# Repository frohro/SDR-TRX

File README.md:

# SDR-TRX Digital Modes Transceiver, 2023-2024
## Philosophy and Design Goals
This SDR is a prototype hardware platform to assist in developing a low-cost transceiver for digital modes (FT8, JSTcall, WSPR, CW, etc) that do not require linear amplification like SSB.  This is designed for amateur radio enthusiasts who view their hobby as an avenue for experimenting, who like building things, and have an interest in HF radio propagation.  The idea is to use a laptop and mainstream (actively maintained) existing software as the display and for the DSP needed.  The hardware described here will fill out the rest of the transceiver.  The assumption is that most hams will have a PC of some kind already, and this is an easy and cheap way to get on the air using the digital modes and their PC.
I am also using this as a platform to demonstrate to my students how to do an electronic design project.  It is hoped a transceiver based on this prototype platform will be inexpensive enough that third-world hams or those with few funds to spend on their hobby would find it attractive.  JLCPCB built five of these for me for a little over $100.  This project is built using designs previously published and would not be possible without them.  The next section is meant to be a short review of some of the projects I found especially useful.
### Previous Work
#### Especially Relevant Work
* [WSJT-Transceiver](https://github.com/agustinmartino/wsjt_transceiver/blob/master/README.md)
* [Quisk SDR Software](https://james.ahlstrom.name/quisk/)
* [WSJT-X Low S/N Digital Mode Decoding Software](https://wsjt.sourceforge.io/)
* [Fldigi](http://www.w1hkj.com/FldigiHelp/index.html)
* [DL2MAN Sandwich](https://dl2man.de/sample-page/)
* [PE1NNZ uSDX](https://github.com/threeme3/usdx)
* [A Comparison of Affordable Self-Assembled SDR Receivers](https://fweb.wallawalla.edu/~frohro/ClassHandouts/Electronics/A%20Comparison%20of%20Affordable,%20Self-Assembled%20%20Software-Defined%20Radio%20Receivers%20Using%20Quadrature%20Sampling%20Down-Conversion.pdf)
* [QRP Labs QDX Transceiver](https://www.qrp-labs.com/qdx.html) (This transceiver is quite similar.)
#### More General but Useful Work
*  [Easy-Transceiver](https://github.com/kholia/Easy-Transceiver])
* [Etherkit JTEncode](https://github.com/etherkit/JTEncode)
* [Etherkit Si5351](https://github.com/etherkit/Si5351Arduino)

###
The basic block diagram showing how this SDR interfaces with a PC is shown below.  (Sorry the photos do not show up on GitHub's README here.  To see them, download the progress notes here: https://github.com/frohro/SDR-TRX/blob/main/SDR-TRX-Readme-Progress-Notes.html and then open them in your browser, or get the iPython Progress Notes for a more up to date version and use JupyterLab or similar tool to read them.)

A clone of the Silicon Labs, Si5351a, the MS5351M is used as the local oscillator for the QSD down converter.  The resultant audio frequency data is sent to the PC where Quisk demodulates it and sends it on to WSJT-X or Fldigi for decoding.  The MS5351M's third oscillator is used to generate the digital signals on transmit.  These signals are amplified by a class E circuit for the 20-meter band.  Throughout the unit, there are features that provide stepping stones toward the final goal.  For example, an output is provided to allow the sound data to be sent to the PC where a sound card on the PC converts the sound signal to digital samples.  A Raspberry Pi Pico or Pico W is used on the SDR to control the MS5351M local oscillator and exciter, sample the receiver audio data using a PCM1808 ADC, and send the sampled data to the PC for processing.  It also receives transmit data from the PC to allow transmission of the digital signals desired.

The Kicad project SDR-TRX contains the hardware documentation, including the schematic diagram and the printed circuit board.  The software is still in development.

##  Transmitter 
The MS5351M, a Si5351a clone, generates a digitally transmitted signal (and the harmonics you expect) on its third output.  It is used to drive a set of CMOS inverters that in turn drive a MOSFET class E amplifier for 20 meters. 

### Class E Amplifier
The design started with the DL2MAN sandwich Class E amplifier for 20 meters.  LTspice was employed to try and minimize the number of values of Extended Parts capacitors needed from JLCPCB while still maintaining a decent efficiency, power output, and harmonic attenuation.  The value of the capacitor that seemed to be best was a 120 pF 100V 1% COG multilayer monolithic capacitor.  We paralleled a bunch to make the amplifier we ended up with.  It was chosen first for harmonic suppression, second for power output, and lastly for efficiency, with the constraint of using only one value of capacitor.  The simulation has about 50 dB of harmonic attenuation, about a watt of output, and an efficiency of 75%.  See the simulation below which is called Class E.asc in the Simulation folder.

This simulation shows the efficiency and output power.

This is the FFT of the antenna voltage.

There is an I2C voltage and current monitor, the INA219A, that should allow measuring the DC power used by the class E amplifier so LTspice simulations can be verified for accuracy easily.

## Receiver
The receiver used was the [QSD Tayloe-type](https://www.norcalqrp.org/files/Tayloe_mixer_x3a.pdf) design using both inverting and inverting inputs.  The inverting input has a lower input impedance and so is more of a current amplifier.  The non-inverting amplifier has a high input impedance, and so acts as a voltage amplifier.  The low-frequency gain of the inverting amplifier is $\frac{-R_f}{R_i}$ and the non-inverting amplifier has a gain of $1 + \frac{R_f}{R_i}$ so the CMRR is  not as good as a fully differential amplifier, but we are just trying to amplify the signal not null out any common mode signal.  We need to keep the DC to $\frac {4.5V}{2}$ and the $1$ term perfectly does this for us for the common mode DC voltage.  There is a gain for the mixer of $1/4$ because the state space average of the switched voltage at the output of the mixer is a quarter of the input voltage.  The gain is initially set to about 20 between the antenna and I or Q.  These signals go into the soundcard or the onboard ADC, a PCM1808.

The MS5351M generates in-phase and quadrature signals for the SN74CBT3253 four-to-one analog switch mixer.

The sampling capacitors provide a low pass filter for the signal, and the cutoff frequency is $1/(2\pi R_f 4 C)$.  The factor of four comes about because the sampling capacitors only get charged a quarter of the time, or equivalently, there are four of them to charge.  The resistance, $R_i$, is the antenna impedance plus the 10 ohms on the inverting input.  The feedback capacitors, $C_f$ add another pole of low pass filter to the signal.  The cutoff frequency of these filters is $1/(2\pi R_f C_f)$.

There are two antenna inputs (BNC connectors), one on a transmit/receive switch that uses the Class E filter to try and filter the received signal, and another one that bypasses the filter that can be used when we want to listen to more than just 20 meters.  It can also suffice to do real-world testing to see which is preferable.

An LDO linear regulator powered by the USB 5 volts or the external 12-volt power supply provides a 4.5 volt low noise power for the analog parts in the receiver.  When the 12-volt input is used the USB power supply is disconnected by some Schottky diodes and two possible regulators drop the voltage to about 5.8 volts to run the rest of the radio except the class E PA stage.  These are selected by an I/O line from the processor or by not populating the undesired supply.  The two options are an SMPS buck regulator or a 7805 linear regulator that is not as efficient but should not produce switching noise. We will experiment to see which we like and choose that one.

There are several ground loop suppression strategies available.  The filtered antenna uses a transformer.  In other places, a jumper is provided to allow a single ground connection through the power supply.  

## Control Circuitry
The control of the SDR comes from the operator via the PC interface software (Quisk, for example), which sends the data to the SDR via USB UART or via WIFI.  The MCU that we chose is the Raspberry Pi Pico or Pico W if WIFI is desired.  It controls the MS5351M programmable oscillator using I2C and uses the INA219 to measure the current and voltage of the power amplifier.  It also reads the ADC via I2S and transfers that data to the PC where Quisk or a similar program demodulates it.  For the Pico, we are using C++ and the Earl E. Philhower, [Arduido-Pico](https://arduino-pico.readthedocs.io/en/latest/index.html) development library.  The easiest way to get started is to use the Arduino IDE, but VScode with Github Copilot there are a lot more features.  You have to [read how to make the Arduino-Pico](https://arduino-pico.readthedocs.io/en/latest/platformio.html) code work with VScode.  The software needs a lot more attention, but that is the point of a software-defined radio.

### PCB
The PCB has test points and uses components I found still available on JLCPCB.  That accounts for why a mix or 0603 and 0805 components, and why there are a lot of 120pF and 4.7nF caps in parallel.

The cutout is for the WIFI antenna if a Pico W is used.

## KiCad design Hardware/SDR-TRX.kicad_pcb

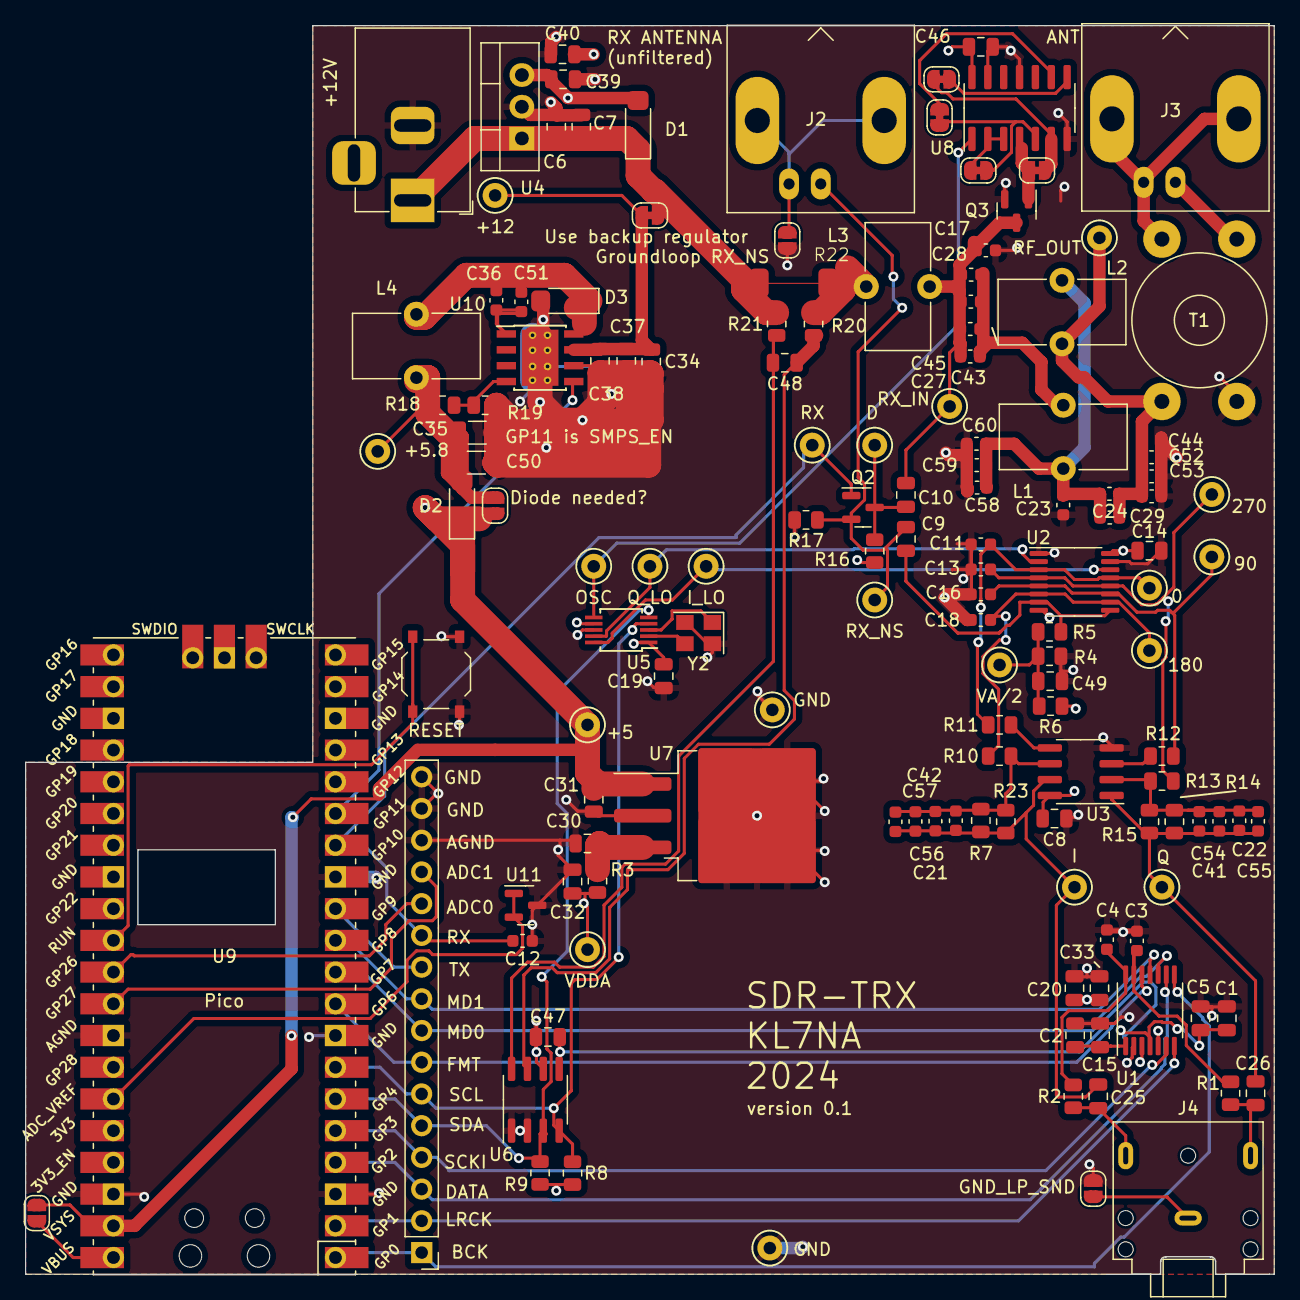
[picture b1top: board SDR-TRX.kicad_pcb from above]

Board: 4 copper layers, 100.0 x 100.0 mm, 141 parts (0 on the bottom side), 69 nets.

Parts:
C1, C2, C6, C20, C30, C32, C39: 10uF; C_0805_2012Metric
C3, C4, C11, C12, C13, C16, C18, C36, C51: 4.7nF; C_0603_1608Metric
C5, C7, C8, C9, C10, C14, C15, C19, C31, C33, C40, C46, C47, C48, C49: 0.1u; C_0805_2012Metric
C17, C21, C22, C23, C24, C27, C28, C29, C41, C42, C43, C44, C45, C52, C53, C54, C55, C56, C57, C58, C59, C60: 120p; C_0603_1608Metric
C25, C26: 1uF; C_0805_2012Metric
C34, C37, C38: 22uF; C_0805_2012Metric
C35, C50: 100uF; C_1206_3216Metric
D1, D2, D3: SS54; DO-214AC-Rob
J1: Debug Connector; PinHeader_1x16_P2.54mm_Vertical
J2, J3: BNC; BNC_Amphenol_B6252HB-NPP3G-50_Horizontal
J4: Audio Out to Soundcard; Jack_3.5mm_CUI_SJ1-3523N_Horizontal
J6: +12V; BarrelJack_Horizontal
JP1: GND_LP_SND; SolderJumper-2_P1.3mm_Open_RoundedPad1.0x1.5mm
JP2: Groundloop RX_NS; SolderJumper-2_P1.3mm_Open_RoundedPad1.0x1.5mm
JP4: Use backup regulator; SolderJumper-2_P1.3mm_Bridged_RoundedPad1.0x1.5mm
JP5: CM1A; SolderJumper-2_P1.3mm_Bridged_RoundedPad1.0x1.5mm
JP6: CM1B; SolderJumper-2_P1.3mm_Bridged_RoundedPad1.0x1.5mm
JP7: CM2B; SolderJumper-2_P1.3mm_Bridged_RoundedPad1.0x1.5mm
JP8: CM2A; SolderJumper-2_P1.3mm_Bridged_RoundedPad1.0x1.5mm
JP9: Diode needed?; SolderJumper-2_P1.3mm_Open_RoundedPad1.0x1.5mm
JP12: USB Only; SolderJumper-2_P1.3mm_Open_RoundedPad1.0x1.5mm
L1: .48uH 12t/T-37-6; L_Toroid_Vertical_L10.0mm_W5.0mm_P5.08mm
L2: .19uH 5t/T37-6; L_Toroid_Vertical_L10.0mm_W5.0mm_P5.08mm
L3: 200u 22t FT-37-43; L_Toroid_Vertical_L10.0mm_W5.0mm_P5.08mm
L4: 15uH 7t/FT37-43; L_Toroid_Vertical_L10.0mm_W5.0mm_P5.08mm
Q2, Q3: IRLML2060; SOT-23
R1, R2: 200; R_0805_2012Metric
R3: 1; R_0805_2012Metric
R4, R5, R6, R18: 10k; R_0805_2012Metric
R7, R14, R15, R23: 3.9k; R_0805_2012Metric
R8, R9: 4.7k; R_0805_2012Metric
R10, R11, R12, R13, R20, R21: 10; R_0805_2012Metric
R16: 470k; R_0805_2012Metric
R17: 1k; R_0805_2012Metric
R19: 2.67k; R_0805_2012Metric
R22: 0.03 shunt; .03 Shunt
SW2: RESET; SW_Push_1P1T_XKB_TS-1187A
T1: 1:1 FT37-43; Transformer_Toroid_Horizontal_D10.5mm_Amidon-T37
TP1: I_LO; TestPoint_Keystone_5000-5004_Miniature
TP2: Q_LO; TestPoint_Keystone_5000-5004_Miniature
TP4: RX_NS; TestPoint_Keystone_5000-5004_Miniature
TP5: 180; TestPoint_Keystone_5000-5004_Miniature
TP6: 0; TestPoint_Keystone_5000-5004_Miniature
TP7: 270; TestPoint_Keystone_5000-5004_Miniature
TP8: 90; TestPoint_Keystone_5000-5004_Miniature
TP9, TP13: GND; TestPoint_Keystone_5000-5004_Miniature
TP10: I; TestPoint_Keystone_5000-5004_Miniature
TP11: Q; TestPoint_Keystone_5000-5004_Miniature
TP12: VA/2; TestPoint_Keystone_5000-5004_Miniature
TP14: RX_IN; TestPoint_Keystone_5000-5004_Miniature
TP15: D; TestPoint_Keystone_5000-5004_Miniature
TP16: OSC; TestPoint_Keystone_5000-5004_Miniature
TP17: RX; TestPoint_Keystone_5000-5004_Miniature
TP18: RF_OUT; TestPoint_Keystone_5000-5004_Miniature
TP27: VDDA; TestPoint_Keystone_5000-5004_Miniature
TP28: +5; TestPoint_Keystone_5000-5004_Miniature
TP34: +5.8; TestPoint_Keystone_5000-5004_Miniature
TP35: +12; TestPoint_Keystone_5000-5004_Miniature
U1: PCM1808PWR; TSSOP-14_4.4x5mm_P0.65mm
U2: SN74CBT3253CPWR; TSSOP-16_4.4x5mm_P0.65mm
U3: OPA1612AxD; SOIC-8_3.9x4.9mm_P1.27mm
U4: LM7805_TO220; TO-220-3_Vertical
U5: MS5351M; MSOP-10_3x3mm_P0.5mm
U6: INA219AxD; SOIC-8_3.9x4.9mm_P1.27mm
U7: LM2937xS; TO-263-3_TabPin2
U8: 74HC14; SOIC-14_3.9x8.7mm_P1.27mm
U9: Pico; RPi_Pico_SMD_TH
U10: TPS5430DDA; TI_SO-PowerPAD-8_ThermalVias
U11: CJ432; SOT-23
Y2: X322525MSB4SI; Crystal_SMD_3225-4Pin_3.2x2.5mm

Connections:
+3.3V: C1.1, C5.2, C19.2, C47.2, R8.2, R9.2, U1.4 (VDD), U5.1 (VDD), U5.7 (VDDO), U6.5 (VS), U9.36 (3V3)
+5V: C31.1, C39.1, C40.2, C46.2, D1.2 (A), D2.1 (K), JP9.2 (B), JP12.2 (B), TP28.1, U4.3 (VO), U7.1 (VI), U8.14 (VCC), U9.39 (VSYS)
+12V: C34.1, C37.1, C38.1, JP4.2 (B), TP35.1, U10.7 (VIN)
/ADC0: J1.12, U9.31 (GPIO26_ADC0)
/ADC1: J1.13, U9.32 (GPIO27_ADC1)
/BCK: J1.1, U1.8 (BCK), U9.1 (GPIO0)
/Class E PA/OSC: TP16.1, U5.6 (CLK2), U8.1
/Class E PA/RX_IN: C10.1, C17.2, C27.2, C28.2, C43.2, C45.2, L3.2, Q3.3 (D), TP14.1
/DATA: J1.3, U1.9 (DOUT), U9.4 (GPIO2)
/FMT: J1.7, U1.12 (FMT), U9.9 (GPIO6)
/LRCK: J1.2, U1.7 (LRCK), U9.2 (GPIO1)
/MD0: J1.8, U1.10 (MD0), U9.10 (GPIO7)
/MD1: J1.9, U1.11 (MD1), U9.11 (GPIO8)
/RX: C12.2, J1.11, Q2.1 (G), TP17.1, U9.14 (GPIO10)
/Receiver/I_OUT: C25.1, J4.R, R2.1
/Receiver/Q_OUT: C26.1, J4.T, R1.1
/Receiver/RX_NS: C9.1, J2.1 (In), Q2.2 (S), R17.1, TP4.1
/SCKI: J1.4, U1.6 (SCKI), U9.5 (GPIO3)
/SCL: J1.6, R8.1, U5.4 (SCL), U6.4 (SCL), U9.7 (GPIO5)
/SDA: J1.5, R9.1, U5.5 (SDA), U6.3 (SDA), U9.6 (GPIO4)
/SMPS_EN: U9.15 (GPIO11), U10.5 (EN)
/TX: J1.10, U9.12 (GPIO9)
GND: C1.2, C2.2, C3.1, C4.1, C5.1, C6.2, C7.1, C8.1, C11.1, C12.1, C13.1, C14.1, C15.1, C16.1, C17.1, C18.1, C19.1, C20.2, C23.2, C30.2, C31.2, C32.2, C33.1, C34.2, C35.2, C37.2, C38.2, C39.2, C40.1, C44.2, C46.1, C47.1, C49.1, C50.2, C52.2, C53.2, C58.2, C59.2, C60.2, D3.2 (A), J1.14, J1.15, J1.16, J6.2, JP1.1 (A), JP2.1 (A), Q3.2 (S), R4.2, R17.2, R19.2, SW2.1 (A), T1.2 (AB), TP9.1, TP13.1, U1.2 (AGND), U1.5 (DGND), U2.1 (1~OE), U2.8 (GND), U2.15 (2~OE), U3.4 (V-), U4.2 (GND), U5.8 (GND), U6.1 (A1), U6.2 (A0), U6.6 (GND), U7.2 (GND), U8.7 (GND), U8.11, U8.13, U9.3 (GND), U9.8 (GND), U9.13 (GND), U9.33 (AGND), U9.38 (GND), U10.6 (GND), U10.9 (GNDPAD), U11.3 (A), Y2.2, Y2.4
unnamed: C21.2, C25.2, C42.2, C56.2, C57.2, R7.1, R23.1, TP10.1, U3.7
unnamed: C22.2, C26.2, C41.2, C54.2, C55.2, R14.1, R15.1, TP11.1, U3.1
unnamed: C23.1, C24.2, C29.2, C58.1, C59.1, C60.1, L1.2, L2.1
unnamed: C27.1, C28.1, C43.1, C45.1, L1.1
unnamed: C49.2, R4.1, R5.1, R6.2, TP12.1
unnamed: C6.1, C7.2, D1.1 (K), J6.1, JP4.1 (A), R21.2, R22.2, U4.1 (VI)
unnamed: C35.1, C50.1, D2.2 (A), JP9.1 (A), L4.2, R18.1, TP34.1
unnamed: C36.1, C51.1, D3.1 (K), L4.1, U10.8 (PH)
unnamed: J2.2 (Ext), JP2.2 (B)
unnamed: J3.2 (Ext), T1.3 (SA)
unnamed: J3.1 (In), T1.4 (SB)
unnamed: J4.S, JP1.2 (B)
unnamed: JP5.1 (A), U8.2, U8.3
unnamed: JP5.2 (B), JP8.1 (A), U8.5
unnamed: JP6.1 (A), Q3.1 (G), U8.4
unnamed: JP6.2 (B), JP7.1 (A), U8.6
unnamed: JP7.2 (B), U8.8
unnamed: JP8.2 (B), U8.9
unnamed: JP12.1 (A), U9.40 (VBUS)
unnamed: L3.1, R20.2, R22.1
unnamed: C10.2, Q2.3 (D), R16.2, TP15.1
unnamed: SW2.2 (B), U9.30 (RUN)
unnamed: C24.1, C29.1, C44.1, C52.1, C53.1, L2.2, T1.1 (AA), TP18.1
unnamed: C3.2, R1.2, U1.13 (VINL)
unnamed: C4.2, R2.2, U1.14 (VINR)
unnamed: C2.1, C15.2, U1.1 (VREF)
unnamed: C9.2, R5.2, U2.7 (1A), U2.9 (2A)
unnamed: C18.2, R10.2, TP5.1, U2.6 (1B1), U2.10 (2B1)
unnamed: C16.2, R12.2, TP8.1, U2.5 (1B2), U2.11 (2B2)
unnamed: C13.2, R13.2, TP7.1, U2.4 (1B3), U2.12 (2B3)
unnamed: C11.2, R11.2, TP6.1, U2.3 (1B4), U2.13 (2B4)
unnamed: TP1.1, U2.14 (S0), U5.10 (CLK0)
unnamed: TP2.1, U2.2 (S1), U5.9 (CLK1)
unnamed: R12.1, U3.3 (+)
unnamed: C22.1, C41.1, C54.1, C55.1, R13.1, R14.2, R15.2, U3.2 (-)
unnamed: R11.1, U3.5 (+)
unnamed: C21.1, C42.1, C56.1, C57.1, R7.2, R10.1, R23.2, U3.6 (-)
unnamed: U5.2 (XA), Y2.3
unnamed: U5.3 (XB), Y2.1
unnamed: C48.2, R21.1, U6.8 (IN+)
unnamed: C48.1, R20.1, U6.7 (IN-)
unnamed: C30.1, R3.2, U7.3 (VO)
unnamed: C36.2, C51.2, U10.1 (BOOT)
unnamed: R18.2, R19.1, U10.4 (VSENSE)
unnamed: U9.35 (ADC_VREF), U11.1 (REF), U11.2 (K)
VDDA: C8.2, C14.2, C20.1, C32.1, C33.2, R3.1, R6.1, R16.1, TP27.1, U1.3 (VCC), U2.16 (VCC), U3.8 (V+)

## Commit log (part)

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2024-04-23 Apr 22, 2024, 9:16 PM
2024-04-23 Apr 22, 2024, 9:19 PM
2024-04-23 Apr 22, 2024, 9:21 PM
2024-04-23 Apr 22, 2024, 9:23 PM
2024-04-23 Apr 22, 2024, 9:24 PM
2024-04-23 Apr 22, 2024, 9:25 PM
2024-04-23 Apr 22, 2024, 9:36 PM
2024-04-23 Apr 22, 2024, 9:41 PM
2024-04-23 Apr 22, 2024, 9:42 PM
2024-04-23 Apr 22, 2024, 9:44 PM
2024-04-23 Apr 22, 2024, 9:50 PM
2024-04-23 Apr 22, 2024, 9:55 PM
2024-04-23 Apr 22, 2024, 10:01 PM
2024-04-23 Apr 22, 2024, 10:03 PM
2024-04-23 Apr 22, 2024, 10:12 PM
2024-04-23 Apr 22, 2024, 10:14 PM
2024-04-23 Apr 22, 2024, 10:25 PM
2024-04-23 Apr 23, 2024, 8:54 AM
2024-04-23 Apr 23, 2024, 10:43 AM
2024-04-23 Apr 23, 2024, 10:46 AM
2024-04-23 Apr 23, 2024, 11:05 AM
2024-04-23 Apr 23, 2024, 11:08 AM
2024-04-23 Apr 23, 2024, 11:10 AM
2024-04-23 Apr 23, 2024, 11:37 AM
2024-04-25 Apr 24, 2024, 10:28 PM
2024-04-25 Apr 25, 2024, 7:40 AM
2024-04-25 Apr 25, 2024, 8:10 AM
2024-04-25 Apr 25, 2024, 8:48 AM
2024-04-25 Apr 25, 2024, 8:53 AM
2024-04-25 Apr 25, 2024, 8:56 AM
2024-04-25 Apr 25, 2024, 9:09 AM
2024-04-25 Apr 25, 2024, 9:10 AM
2024-04-25 Apr 25, 2024, 9:12 AM
2024-04-25 Apr 25, 2024, 10:24 AM
2024-04-25 Apr 25, 2024, 10:27 AM
2024-04-25 Apr 25, 2024, 10:43 AM
2024-04-25 Apr 25, 2024, 10:50 AM
2024-04-25 Apr 25, 2024, 10:53 AM
2024-04-25 Apr 25, 2024, 10:57 AM
2024-04-25 Apr 25, 2024, 10:59 AM
2024-04-25 Apr 25, 2024, 11:00 AM
2024-04-25 Apr 25, 2024, 11:02 AM
2024-04-25 Apr 25, 2024, 11:04 AM
2024-04-25 Apr 25, 2024, 11:06 AM
2024-04-25 Apr 25, 2024, 11:08 AM
2024-04-25 Apr 25, 2024, 11:09 AM
2024-04-25 Apr 25, 2024, 11:11 AM
2024-04-25 Apr 25, 2024, 11:14 AM
2024-04-25 Apr 25, 2024, 11:21 AM
2024-04-25 Apr 25, 2024, 11:23 AM
2024-04-25 Apr 25, 2024, 11:25 AM
2024-04-25 Apr 25, 2024, 11:26 AM
2024-04-25 Apr 25, 2024, 11:27 AM
2024-04-25 Apr 25, 2024, 11:31 AM
2024-04-25 Apr 25, 2024, 11:34 AM
2024-04-25 Apr 25, 2024, 11:36 AM
2024-04-25 Apr 25, 2024, 11:39 AM
2024-04-25 Apr 25, 2024, 11:40 AM
2024-04-25 Apr 25, 2024, 11:41 AM
2024-04-25 Apr 25, 2024, 11:43 AM
2024-04-25 Apr 25, 2024, 11:45 AM
2024-04-25 Apr 25, 2024, 11:46 AM
2024-04-25 Apr 25, 2024, 12:27 PM
2024-04-25 Apr 25, 2024, 12:31 PM
2024-04-25 Apr 25, 2024, 12:35 PM
2024-04-25 Apr 25, 2024, 12:36 PM
2024-04-25 Apr 25, 2024, 12:42 PM
2024-04-25 Apr 25, 2024, 12:43 PM
2024-04-25 Apr 25, 2024, 1:20 PM
2024-04-25 Apr 25, 2024, 1:22 PM
2024-04-25 Apr 25, 2024, 1:31 PM
2024-04-25 Apr 25, 2024, 1:38 PM
2024-04-25 Apr 25, 2024, 1:39 PM
2024-04-25 Apr 25, 2024, 1:40 PM
2024-04-25 Apr 25, 2024, 1:41 PM
2024-04-25 Apr 25, 2024, 1:44 PM
2024-04-25 Apr 25, 2024, 1:45 PM
2024-04-25 Apr 25, 2024, 1:51 PM
2024-04-25 Apr 25, 2024, 1:54 PM
2024-04-25 Apr 25, 2024, 1:58 PM
2024-04-25 Apr 25, 2024, 4:00 PM
2024-04-25 Apr 25, 2024, 4:04 PM
2024-04-25 Apr 25, 2024, 4:06 PM
2024-04-25 Apr 25, 2024, 4:07 PM
2024-04-25 Apr 25, 2024, 4:08 PM
2024-04-25 Apr 25, 2024, 4:09 PM
2024-04-25 Apr 25, 2024, 4:12 PM
2024-04-25 Apr 25, 2024, 4:13 PM
2024-04-25 Apr 25, 2024, 4:15 PM
2024-04-25 Apr 25, 2024, 4:17 PM
2024-04-25 Apr 25, 2024, 4:22 PM
2024-04-25 Apr 25, 2024, 4:25 PM
2024-04-25 Apr 25, 2024, 4:27 PM
2024-04-25 Apr 25, 2024, 4:28 PM
2024-04-25 Apr 25, 2024, 4:30 PM
2024-04-25 Apr 25, 2024, 4:32 PM
2024-04-25 Apr 25, 2024, 4:39 PM
2024-04-25 Apr 25, 2024, 4:46 PM
2024-04-25 Apr 25, 2024, 4:47 PM
2024-04-25 Apr 25, 2024, 4:49 PM
2024-04-26 Apr 25, 2024, 6:13 PM
2024-04-26 Apr 25, 2024, 6:15 PM
2024-04-26 Apr 25, 2024, 6:16 PM
2024-04-26 Apr 25, 2024, 6:19 PM
2024-04-26 Apr 25, 2024, 6:21 PM
2024-04-26 Apr 25, 2024, 6:23 PM
2024-04-26 Apr 25, 2024, 6:26 PM
2024-04-26 Apr 25, 2024, 6:29 PM
2024-04-26 Apr 25, 2024, 6:30 PM
2024-04-26 Apr 25, 2024, 6:32 PM
2024-04-26 Apr 25, 2024, 6:35 PM
2024-04-26 Apr 25, 2024, 6:36 PM
2024-04-26 Apr 25, 2024, 6:39 PM
2024-04-26 Apr 25, 2024, 6:42 PM
2024-04-26 Apr 25, 2024, 6:44 PM
2024-04-26 Apr 25, 2024, 6:47 PM
2024-04-26 Apr 25, 2024, 6:50 PM
2024-04-26 Apr 25, 2024, 6:51 PM
2024-04-26 Apr 25, 2024, 6:53 PM
2024-04-26 Apr 25, 2024, 6:57 PM
2024-04-26 Apr 25, 2024, 6:58 PM
2024-04-26 Apr 25, 2024, 7:02 PM
2024-04-26 Apr 25, 2024, 7:03 PM
2024-04-26 Apr 25, 2024, 7:06 PM
2024-04-26 Apr 25, 2024, 7:08 PM
2024-04-26 Apr 25, 2024, 7:17 PM
2024-04-26 Apr 25, 2024, 7:29 PM
2024-04-26 Apr 25, 2024, 7:42 PM
2024-04-26 Apr 25, 2024, 7:44 PM
2024-04-26 Apr 25, 2024, 8:00 PM
2024-04-26 Apr 25, 2024, 8:06 PM
2024-04-26 Apr 25, 2024, 8:45 PM
2024-04-26 Apr 25, 2024, 10:01 PM
2024-04-26 Apr 25, 2024, 10:02 PM
2024-04-26 Apr 25, 2024, 10:03 PM
2024-04-26 Apr 25, 2024, 10:07 PM
2024-04-26 Apr 25, 2024, 10:08 PM
2024-04-26 Apr 25, 2024, 10:09 PM
2024-04-26 Apr 25, 2024, 10:10 PM
2024-04-26 Apr 25, 2024, 10:11 PM
2024-04-26 Apr 25, 2024, 10:13 PM
2024-04-26 Apr 25, 2024, 10:24 PM
2024-04-26 Apr 25, 2024, 10:27 PM
2024-04-26 Apr 25, 2024, 10:29 PM
2024-04-26 Apr 25, 2024, 10:32 PM
2024-04-26 Apr 25, 2024, 10:34 PM
2024-04-26 Apr 25, 2024, 10:36 PM
2024-04-26 Apr 25, 2024, 10:37 PM
2024-04-26 Apr 25, 2024, 10:39 PM
2024-04-26 Apr 25, 2024, 10:45 PM
2024-04-26 Apr 25, 2024, 10:46 PM
2024-04-27 Apr 27, 2024, 2:48 PM
2024-04-27 Apr 27, 2024, 2:50 PM
2024-04-27 Apr 27, 2024, 3:05 PM
2024-04-28 Apr 28, 2024, 2:27 PM
2024-04-28 Apr 28, 2024, 2:29 PM
2024-04-28 Apr 28, 2024, 2:31 PM
2024-04-28 Apr 28, 2024, 2:34 PM
2024-04-28 Apr 28, 2024, 2:37 PM
2024-04-28 Apr 28, 2024, 2:42 PM
2024-04-28 Apr 28, 2024, 2:55 PM
2024-04-28 Apr 28, 2024, 2:56 PM
2024-04-28 Apr 28, 2024, 3:29 PM
2024-04-29 Apr 28, 2024, 5:55 PM
2024-04-29 Apr 28, 2024, 5:59 PM
2024-04-29 Apr 28, 2024, 6:04 PM
2024-04-29 Apr 28, 2024, 6:07 PM
2024-04-29 Apr 28, 2024, 6:08 PM
2024-04-29 Apr 28, 2024, 6:09 PM
2024-04-29 Apr 28, 2024, 6:15 PM
2024-04-29 Apr 28, 2024, 6:18 PM
2024-04-29 Apr 28, 2024, 6:19 PM
2024-04-29 Apr 28, 2024, 6:20 PM
2024-04-29 Apr 28, 2024, 6:21 PM
2024-04-29 Apr 28, 2024, 6:24 PM
2024-04-29 Apr 28, 2024, 6:26 PM
2024-04-29 Apr 28, 2024, 6:28 PM
2024-04-29 Apr 28, 2024, 6:30 PM
2024-04-29 Apr 28, 2024, 6:33 PM
2024-04-29 Apr 28, 2024, 6:35 PM
2024-04-29 Apr 28, 2024, 6:42 PM
2024-04-29 Apr 28, 2024, 6:44 PM
2024-04-29 Apr 28, 2024, 6:55 PM
2024-04-29 Apr 28, 2024, 6:57 PM
2024-04-29 Apr 28, 2024, 8:07 PM
2024-04-29 Apr 28, 2024, 8:18 PM
2024-04-29 Apr 28, 2024, 10:03 PM
2024-04-29 Apr 28, 2024, 10:10 PM
2024-04-29 Apr 28, 2024, 10:11 PM
2024-04-29 Apr 28, 2024, 10:19 PM
2024-04-29 Apr 28, 2024, 10:22 PM
2024-04-29 Apr 28, 2024, 10:24 PM
2024-04-29 Apr 29, 2024, 7:33 AM
2024-04-29 Apr 29, 2024, 7:36 AM
2024-04-29 Apr 29, 2024, 7:37 AM
2024-04-29 Apr 29, 2024, 7:39 AM
2024-04-29 Apr 29, 2024, 7:41 AM
2024-04-29 Apr 29, 2024, 7:42 AM
2024-04-29 Apr 29, 2024, 7:45 AM
2024-04-29 Apr 29, 2024, 7:46 AM
2024-04-29 Apr 29, 2024, 7:54 AM
2024-04-29 Apr 29, 2024, 7:56 AM
2024-04-29 Apr 29, 2024, 7:58 AM
2024-04-29 Apr 29, 2024, 8:02 AM
2024-04-29 Apr 29, 2024, 8:03 AM
2024-04-29 Apr 29, 2024, 8:04 AM
2024-04-29 Apr 29, 2024, 8:07 AM
2024-04-29 Apr 29, 2024, 8:10 AM
2024-04-29 Apr 29, 2024, 8:11 AM
2024-04-29 Apr 29, 2024, 8:12 AM
2024-04-29 Apr 29, 2024, 8:13 AM
2024-04-29 Apr 29, 2024, 8:14 AM
2024-04-29 Apr 29, 2024, 8:19 AM
2024-04-29 Apr 29, 2024, 8:21 AM
2024-04-29 Apr 29, 2024, 8:23 AM
2024-04-29 Apr 29, 2024, 8:27 AM
2024-04-29 Apr 29, 2024, 8:29 AM
2024-04-29 Apr 29, 2024, 8:31 AM
2024-04-29 Apr 29, 2024, 8:48 AM
2024-04-29 Apr 29, 2024, 8:50 AM
2024-04-29 Apr 29, 2024, 8:55 AM
2024-04-29 Apr 29, 2024, 8:58 AM
2024-04-29 Apr 29, 2024, 9:00 AM
2024-04-29 Apr 29, 2024, 9:04 AM
2024-04-29 Apr 29, 2024, 9:06 AM
2024-04-29 Apr 29, 2024, 9:08 AM
2024-04-29 Apr 29, 2024, 9:09 AM
2024-04-29 Apr 29, 2024, 9:20 AM
2024-04-29 Apr 29, 2024, 9:22 AM
2024-04-29 Apr 29, 2024, 9:25 AM
2024-04-29 Apr 29, 2024, 9:26 AM
2024-04-29 Apr 29, 2024, 9:28 AM
2024-04-29 Apr 29, 2024, 9:35 AM
2024-04-29 Apr 29, 2024, 9:36 AM
2024-04-29 Apr 29, 2024, 10:27 AM
2024-04-29 Apr 29, 2024, 10:29 AM
2024-04-29 Apr 29, 2024, 11:02 AM
2024-04-29 Apr 29, 2024, 11:19 AM
2024-04-29 Apr 29, 2024, 11:22 AM
2024-04-29 Apr 29, 2024, 12:42 PM
2024-04-29 Apr 29, 2024, 12:43 PM
2024-04-29 Apr 29, 2024, 12:52 PM
2024-04-29 Apr 29, 2024, 1:16 PM
2024-04-29 Apr 29, 2024, 1:56 PM
2024-04-29 Apr 29, 2024, 1:57 PM
2024-04-29 Apr 29, 2024, 2:01 PM
2024-04-29 Apr 29, 2024, 2:03 PM
2024-04-29 Apr 29, 2024, 2:07 PM
2024-04-29 Apr 29, 2024, 2:10 PM
2024-04-29 Apr 29, 2024, 2:11 PM
2024-04-29 Apr 29, 2024, 2:17 PM
2024-04-29 Apr 29, 2024, 2:20 PM
2024-04-29 Apr 29, 2024, 2:25 PM
2024-04-29 Apr 29, 2024, 2:28 PM
2024-04-29 Apr 29, 2024, 2:29 PM
2024-04-29 Apr 29, 2024, 2:32 PM
2024-04-29 Apr 29, 2024, 2:35 PM
2024-04-29 Apr 29, 2024, 2:40 PM
2024-04-29 Apr 29, 2024, 2:41 PM
2024-04-29 Apr 29, 2024, 2:42 PM
2024-04-29 Apr 29, 2024, 2:48 PM
2024-04-29 Apr 29, 2024, 2:51 PM
2024-05-05 My automatic commits seem to have stopped. So manually doing it.
2024-05-05 adding the Python Test Files.
2024-05-09 Sending UDP data to Quisk now works.
2024-05-09 Added autodetect on the IP address of the SDR-TRX to the Quisk hardware file.
2024-05-10 Some features to make changing Access Points easier.
2024-05-10 May 9, 2024, 9:21 PM
2024-05-10 May 9, 2024, 9:28 PM
2024-05-10 May 9, 2024, 9:33 PM
2024-05-10 May 9, 2024, 10:23 PM
2024-05-10 May 9, 2024, 10:46 PM
2024-05-10 May 9, 2024, 10:48 PM
2024-05-10 May 9, 2024, 11:16 PM
2024-05-10 May 9, 2024, 11:21 PM
2024-05-10 May 9, 2024, 11:26 PM
2024-05-10 May 9, 2024, 11:41 PM
2024-05-10 May 9, 2024, 11:45 PM
2024-05-10 May 9, 2024, 11:47 PM
2024-05-10 May 9, 2024, 11:49 PM
2024-05-10 May 9, 2024, 11:55 PM
2024-05-10 May 10, 2024, 8:48 AM
2024-05-10 May 10, 2024, 8:51 AM
2024-05-10 May 10, 2024, 8:52 AM
2024-05-10 May 10, 2024, 8:59 AM
2024-05-10 May 10, 2024, 9:02 AM
2024-05-10 May 10, 2024, 9:13 AM
2024-05-10 May 10, 2024, 9:22 AM
2024-05-10 May 10, 2024, 9:38 AM
2024-05-10 May 10, 2024, 9:43 AM
2024-05-10 May 10, 2024, 9:49 AM
2024-05-10 May 10, 2024, 9:51 AM
2024-05-10 May 10, 2024, 9:54 AM
2024-05-10 May 10, 2024, 10:07 AM
2024-05-10 May 10, 2024, 10:12 AM
2024-05-10 May 10, 2024, 10:23 AM
2024-05-10 May 10, 2024, 10:29 AM
2024-05-10 May 10, 2024, 10:40 AM
2024-05-10 May 10, 2024, 10:41 AM
2024-05-10 May 10, 2024, 10:43 AM
2024-05-10 May 10, 2024, 10:44 AM
2024-05-10 May 10, 2024, 11:14 AM
2024-05-12 May 12, 2024, 1:06 PM
2024-05-13 May 13, 2024, 12:24 PM
2024-05-13 May 13, 2024, 12:31 PM
2024-05-13 May 13, 2024, 12:34 PM
2024-05-13 May 13, 2024, 12:38 PM
2024-05-13 May 13, 2024, 12:45 PM
2024-05-13 May 13, 2024, 12:50 PM
2024-05-13 May 13, 2024, 12:52 PM
2024-05-13 May 13, 2024, 12:57 PM
2024-05-13 May 13, 2024, 1:31 PM
2024-05-13 May 13, 2024, 1:37 PM
2024-05-13 May 13, 2024, 1:40 PM
2024-05-13 May 13, 2024, 2:02 PM
2024-05-13 May 13, 2024, 2:07 PM
2024-05-13 May 13, 2024, 2:09 PM
2024-05-13 May 13, 2024, 2:10 PM
2024-05-13 May 13, 2024, 2:13 PM
2024-05-14 May 14, 2024, 7:36 AM
2024-05-14 May 14, 2024, 7:41 AM
2024-05-14 May 14, 2024, 8:22 AM
2024-05-14 May 14, 2024, 8:26 AM
2024-05-14 May 14, 2024, 2:06 PM
2024-05-14 May 14, 2024, 2:08 PM
2024-05-14 May 14, 2024, 3:44 PM
2024-05-14 May 14, 2024, 3:47 PM
2024-05-14 May 14, 2024, 3:48 PM
2024-05-14 May 14, 2024, 3:51 PM
2024-05-14 May 14, 2024, 3:58 PM
2024-05-16 May 16, 2024, 10:21 AM
2024-05-16 May 16, 2024, 10:27 AM
2024-05-16 May 16, 2024, 10:31 AM
2024-05-16 May 16, 2024, 10:41 AM
2024-05-16 May 16, 2024, 10:43 AM
2024-05-16 May 16, 2024, 11:06 AM
2024-05-16 May 16, 2024, 11:08 AM
2024-05-16 May 16, 2024, 11:10 AM
2024-05-16 May 16, 2024, 11:12 AM
2024-05-16 May 16, 2024, 11:14 AM
2024-05-16 May 16, 2024, 12:34 PM
2024-05-16 May 16, 2024, 4:37 PM
2024-05-17 May 17, 2024, 6:20 AM
2024-05-17 May 17, 2024, 1:14 PM
2024-05-17 May 17, 2024, 1:15 PM
2024-05-18 May 17, 2024, 10:08 PM
2024-05-19 Added html of progress notes.
2024-05-19 May 19, 2024, 1:57 PM
2024-05-20 May 20, 2024, 8:16 AM
2024-05-20 May 20, 2024, 8:17 AM
2024-05-21 Update README.md
    Explained where to get the photos for the readme.
2024-05-26 May 25, 2024, 8:47 PM
2024-05-26 May 25, 2024, 8:48 PM
2024-05-26 May 25, 2024, 8:49 PM
2024-05-26 May 25, 2024, 8:50 PM
2024-05-26 May 25, 2024, 8:51 PM
2024-05-26 May 25, 2024, 8:52 PM
2024-05-26 May 25, 2024, 9:19 PM
2024-05-26 May 26, 2024, 7:27 AM
2024-05-26 May 26, 2024, 7:49 AM
2024-05-26 May 26, 2024, 8:08 AM
2024-05-28 May 28, 2024, 3:20 PM
2024-05-31 May 30, 2024, 6:01 PM
2024-05-31 May 30, 2024, 6:27 PM
2024-07-01 Jul 1, 2024, 1:31 PM
